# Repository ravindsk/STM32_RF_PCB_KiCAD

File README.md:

# STM32_RF_PCB_KiCAD
#Custom PCB for transceiver NRF24L01
#Check description.docx for more information

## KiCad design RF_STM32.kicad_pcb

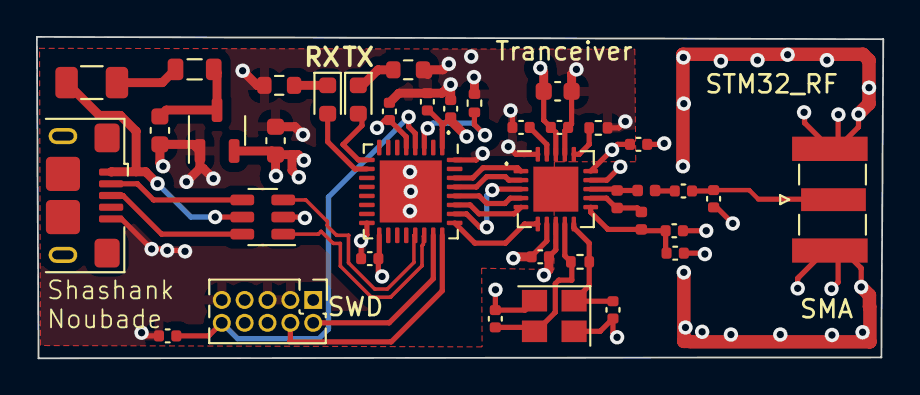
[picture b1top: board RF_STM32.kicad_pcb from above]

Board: 4 copper layers, 47.0 x 17.9 mm, 38 parts (0 on the bottom side), 32 nets.

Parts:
C1, C2, C9: 10u; C_0603_1608Metric
C3: 1u; C_0402_1005Metric
C4, C5, C6, C7: 100n; C_0402_1005Metric
C8: 33n; C_0402_1005Metric
C10, C11, C12: 10n; C_0402_1005Metric
C13, C14: 12p; C_0402_1005Metric
C15: 2n2; C_0402_1005Metric
C16: 4p7; C_0402_1005Metric
C17: 1p5; C_0402_1005Metric
C18: 1p; C_0402_1005Metric
D1: GR; LED_0603_1608Metric
D2: YE; LED_0603_1608Metric
F1: 100mA; Fuse_1206_3216Metric
FB1: 100@100Mhz; L_0805_2012Metric
J1: USB_B_Micro; USB_Micro-B_Amphenol_10118193-0001LF_Horizontal
J2: ARM 10pin; PinHeader_2x05_P1.27mm_Vertical
J3: SMA; SMA_Samtec_SMA-J-P-X-ST-EM1_EdgeMount
L1: 8n2; L_0402_1005Metric
L2: 3n9; L_0402_1005Metric
L3: 2n7; L_0402_1005Metric
R1: 10k; R_0402_1005Metric
R2, R3: 2k2; R_0603_1608Metric
R4: 22k; R_0402_1005Metric
R5: 1M; R_0402_1005Metric
U1: XC6206PxxxMR; SOT-23-3
U2: USBLC6-2SC6; SOT-23-6
U3: STM32L432KBUx; QFN-32-1EP_5x5mm_P0.5mm_EP3.45x3.45mm
U4: nRF24L01P; QFN-20-1EP_4x4mm_P0.5mm_EP2.5x2.5mm
Y1: 16MHz; Crystal_SMD_3225-4Pin_3.2x2.5mm

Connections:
+3V3: C2.1, C3.1, C4.1, C5.1, C6.1, C9.1, C10.1, C11.1, C12.1, J2.1, U1.2 (VO), U3.1 (VDD), U3.5 (VDDA), U3.17 (VDD), U4.7 (VDD), U4.15 (VDD), U4.18 (VDD)
+5V: F1.2, J1.1 (VBUS), U2.5 (VBUS)
ANT1: L1.2, L3.2, U4.12 (ANT1)
ANT2: L1.1, L2.1, U4.13 (ANT2)
GND: C1.2, C2.2, C3.2, C4.2, C5.2, C6.2, C7.2, C8.2, C9.2, C10.2, C11.2, C12.2, C13.2, C14.2, C15.1, C16.1, C18.1, J1.5 (GND), J2.3, J2.5, J2.9, J3.2 (Ext), R1.2, R2.2, R3.2, R4.2, U1.1 (GND), U2.2 (GND), U3.16 (VSS), U3.32 (VSS), U3.33 (VSS), U4.8 (VSS), U4.14 (VSS), U4.17 (VSS), U4.20 (VSS), Y1.2, Y1.4
NRF_CE: U3.30 (PB7), U4.1 (CE)
NRF_IRQ: U3.25 (PA15), U4.6 (IRQ)
NRST: C7.1, J2.10, U3.4 (NRST)
unnamed: C17.2, L2.2
unnamed: D1.2 (A), U3.10 (PA4)
unnamed: D1.1 (K), R2.1
unnamed: D2.2 (A), U3.9 (PA3)
unnamed: D2.1 (K), R3.1
unnamed: F1.1, FB1.1
unnamed: C17.1, C18.2, J3.1 (In)
unnamed: C1.1, FB1.2, U1.3 (VI)
unnamed: R1.1, U3.3 (PC15)
unnamed: C8.1, U4.19 (DVDD)
unnamed: R4.1, U4.16 (IREF)
SPI3_!CS: U3.29 (PB6), U4.2 (CSN)
SPI3_MISO: U3.27 (PB4), U4.5 (MISO)
SPI3_MOSI: U3.28 (PB5), U4.4 (MOSI)
SPI3_SCK: U3.26 (PB3), U4.3 (SCK)
SWCLK: J2.4, U3.24 (PA14)
SWDIO: J2.2, U3.23 (PA13)
USB_CONN_D+: J1.3 (D+), U2.6 (I/O1)
USB_CONN_D-: J1.2 (D-), U2.4 (I/O2)
USB_D+: U2.1 (I/O1), U3.22 (PA12)
USB_D-: U2.3 (I/O2), U3.21 (PA11)
VDD_PA: C15.2, C16.2, L3.1, U4.11 (VDD_PA)
XC1: C13.1, R5.2, U4.10 (XC1), Y1.1
XC2: C14.1, R5.1, U4.9 (XC2), Y1.3

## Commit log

2023-09-21 Information
2023-09-21 Gerber files
2023-09-21 Assembly files
2023-09-21 3D_View
2023-09-21 Schematic_File
2023-09-21 PCB_file
2023-09-21 Complete file
2023-09-21 Description document
